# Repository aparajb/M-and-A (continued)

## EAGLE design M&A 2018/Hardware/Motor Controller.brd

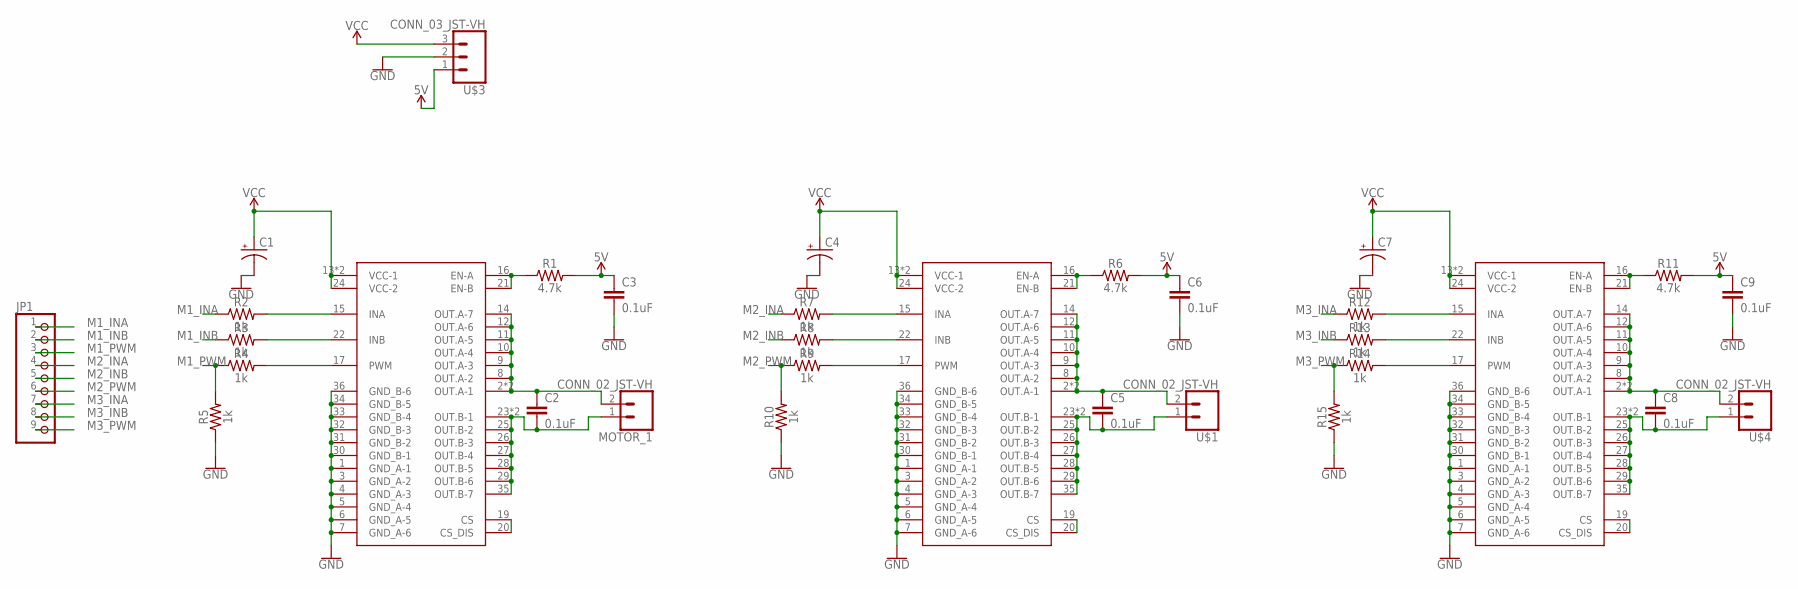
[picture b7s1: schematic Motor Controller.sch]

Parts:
C1, C4, C7: CPOL-USE3.5-8; E3,5-8
C2, C3, C5, C6, C8, C9: 0.1uF; 0603
JP1: PINHD-1X9; 1X09
M1: M1; SOP50P1030X247-36N
M2: M2; SOP50P1030X247-36N
M3: M3; SOP50P1030X247-36N
MOTOR_1: CONN_02_JST-VH; B2P-VH
R1, R6, R11: 4.7k; 0603
R2, R3, R4, R5, R7, R8, R9, R10, R12, R13, R14, R15: 1k; 0603
U$1, U$4: CONN_02_JST-VH; B2P-VH
U$3: CONN_03_JST-VH; B3P-VH

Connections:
5V: C3.1, C6.1, C9.1, R1.2, R6.2, R11.2, U$3.1
GND: C1.-, C3.2, C4.-, C6.2, C7.-, C9.2, M1.1 (GND_A-1), M1.3 (GND_A-2), M1.4 (GND_A-3), M1.5 (GND_A-4), M1.6 (GND_A-5), M1.7 (GND_A-6), M1.30 (GND_B-1), M1.31 (GND_B-2), M1.32 (GND_B-3), M1.33 (GND_B-4), M1.34 (GND_B-5), M1.36 (GND_B-6), M2.1 (GND_A-1), M2.3 (GND_A-2), M2.4 (GND_A-3), M2.5 (GND_A-4), M2.6 (GND_A-5), M2.7 (GND_A-6), M2.30 (GND_B-1), M2.31 (GND_B-2), M2.32 (GND_B-3), M2.33 (GND_B-4), M2.34 (GND_B-5), M2.36 (GND_B-6), M3.1 (GND_A-1), M3.3 (GND_A-2), M3.4 (GND_A-3), M3.5 (GND_A-4), M3.6 (GND_A-5), M3.7 (GND_A-6), M3.30 (GND_B-1), M3.31 (GND_B-2), M3.32 (GND_B-3), M3.33 (GND_B-4), M3.34 (GND_B-5), M3.36 (GND_B-6), R5.1, R10.1, R15.1, U$3.2
M1_INA: JP1.1, R2.1
M1_INB: JP1.2, R3.1
M1_PWM: JP1.3, R4.1, R5.2
M2_INA: JP1.4, R7.1
M2_INB: JP1.5, R8.1
M2_PWM: JP1.6, R9.1, R10.2
M3_INA: JP1.7, R12.1
M3_INB: JP1.8, R13.1
M3_PWM: JP1.9, R14.1, R15.2
unnamed: C5.1, M2.2 (OUT.A-1), M2.8 (OUT.A-2), M2.9 (OUT.A-3), M2.10 (OUT.A-4), M2.11 (OUT.A-5), M2.12 (OUT.A-6), M2.14 (OUT.A-7), M2.SLUG2 (OUT.A-1), U$1.2
unnamed: C2.1, M1.2 (OUT.A-1), M1.8 (OUT.A-2), M1.9 (OUT.A-3), M1.10 (OUT.A-4), M1.11 (OUT.A-5), M1.12 (OUT.A-6), M1.14 (OUT.A-7), M1.SLUG2 (OUT.A-1), MOTOR_1.2
unnamed: C2.2, M1.23 (OUT.B-1), M1.25 (OUT.B-2), M1.26 (OUT.B-3), M1.27 (OUT.B-4), M1.28 (OUT.B-5), M1.29 (OUT.B-6), M1.35 (OUT.B-7), M1.SLUG3 (OUT.B-1), MOTOR_1.1
unnamed: M1.19 (CS), M1.20 (CS_DIS)
unnamed: M1.16 (EN-A), M1.21 (EN-B), R1.1
unnamed: C5.2, M2.23 (OUT.B-1), M2.25 (OUT.B-2), M2.26 (OUT.B-3), M2.27 (OUT.B-4), M2.28 (OUT.B-5), M2.29 (OUT.B-6), M2.35 (OUT.B-7), M2.SLUG3 (OUT.B-1), U$1.1
unnamed: M2.19 (CS), M2.20 (CS_DIS)
unnamed: M1.15 (INA), R2.2
unnamed: M1.22 (INB), R3.2
unnamed: M1.17 (PWM), R4.2
unnamed: M2.16 (EN-A), M2.21 (EN-B), R6.1
unnamed: M2.15 (INA), R7.2
unnamed: M2.22 (INB), R8.2
unnamed: M2.17 (PWM), R9.2
unnamed: C8.1, M3.2 (OUT.A-1), M3.8 (OUT.A-2), M3.9 (OUT.A-3), M3.10 (OUT.A-4), M3.11 (OUT.A-5), M3.12 (OUT.A-6), M3.14 (OUT.A-7), M3.SLUG2 (OUT.A-1), U$4.2
unnamed: C8.2, M3.23 (OUT.B-1), M3.25 (OUT.B-2), M3.26 (OUT.B-3), M3.27 (OUT.B-4), M3.28 (OUT.B-5), M3.29 (OUT.B-6), M3.35 (OUT.B-7), M3.SLUG3 (OUT.B-1), U$4.1
unnamed: M3.19 (CS), M3.20 (CS_DIS)
unnamed: M3.16 (EN-A), M3.21 (EN-B), R11.1
unnamed: M3.15 (INA), R12.2
unnamed: M3.22 (INB), R13.2
unnamed: M3.17 (PWM), R14.2
VCC: C1.+, C4.+, C7.+, M1.13 (VCC-1), M1.24 (VCC-2), M1.SLUG1 (VCC-1), M2.13 (VCC-1), M2.24 (VCC-2), M2.SLUG1 (VCC-1), M3.13 (VCC-1), M3.24 (VCC-2), M3.SLUG1 (VCC-1), U$3.3

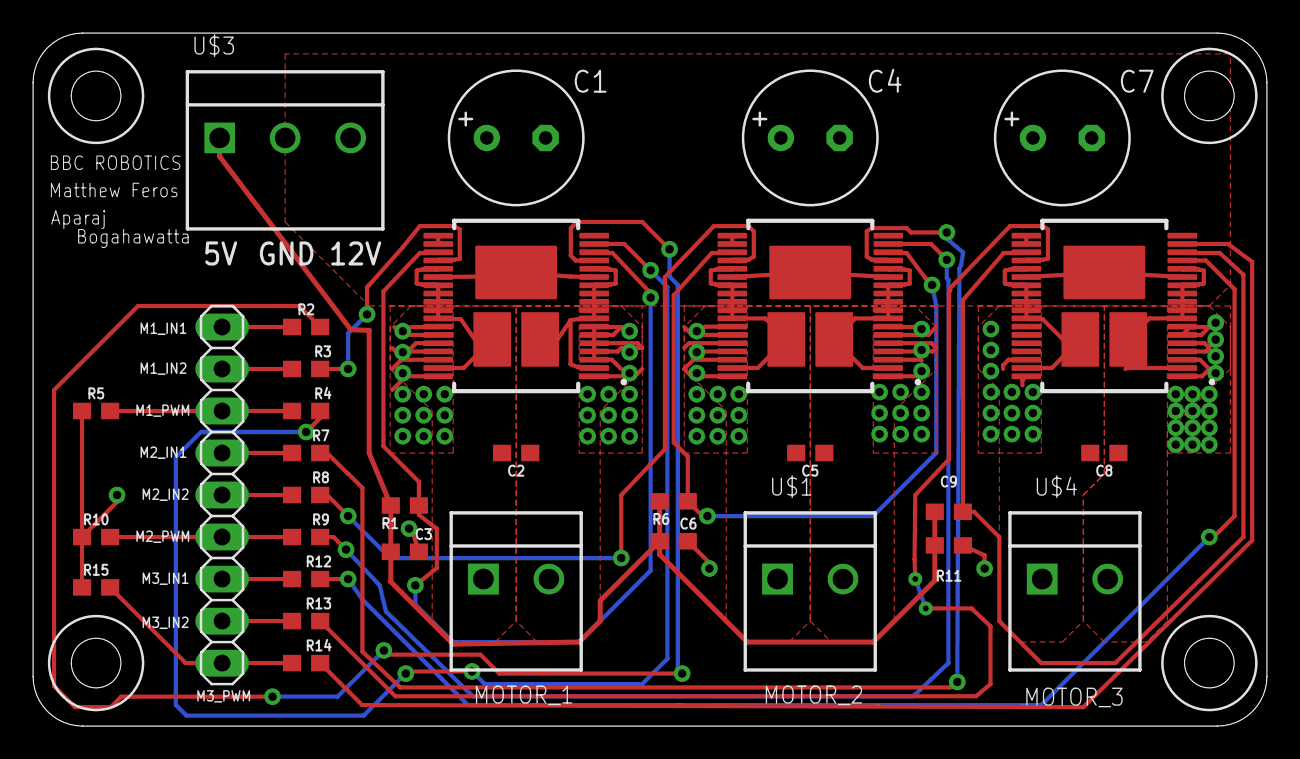
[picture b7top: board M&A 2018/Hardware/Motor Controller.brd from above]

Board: 2 copper layers, 74.6 x 41.9 mm, 32 parts (0 on the bottom side), 33 nets.

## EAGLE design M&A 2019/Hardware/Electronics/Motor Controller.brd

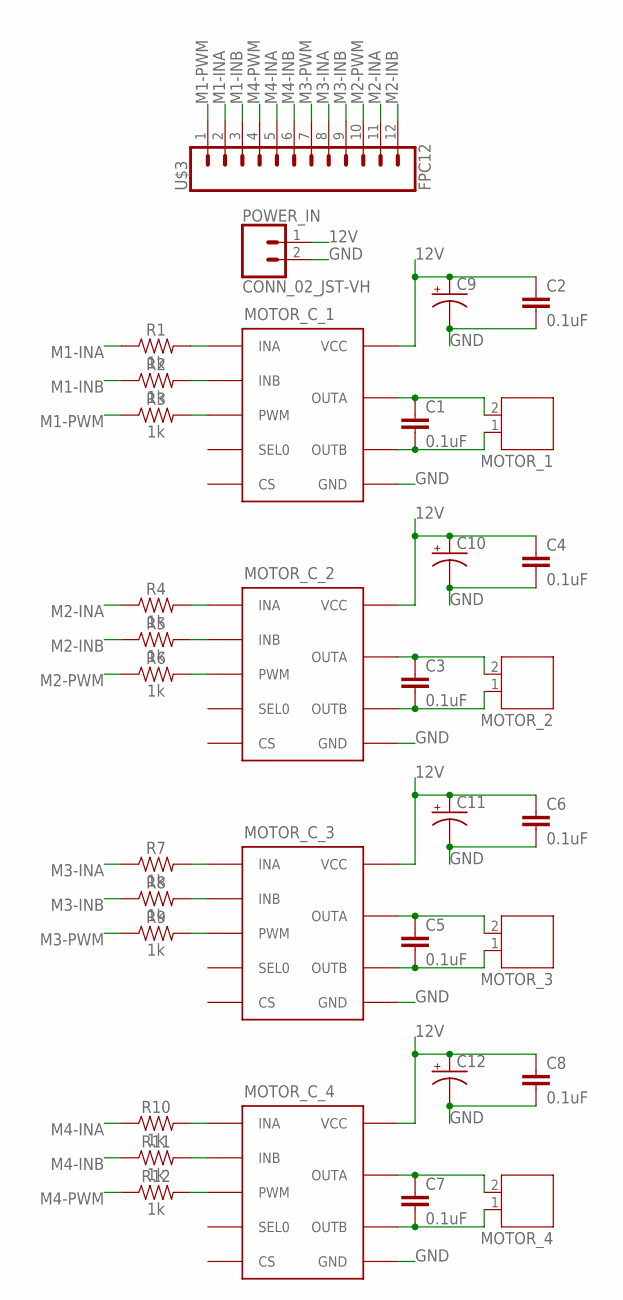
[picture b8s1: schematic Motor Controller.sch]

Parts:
C1, C2, C3, C4, C5, C6, C7, C8: 0.1uF; 0603
C9, C10, C11, C12: CPOL-USE3.5-8; E3,5-8
MOTOR_1, MOTOR_2, MOTOR_3, MOTOR_4: JST-PH2
MOTOR_C_1, MOTOR_C_2, MOTOR_C_3, MOTOR_C_4: VNH7100BASTR; SO-16
POWER_IN: CONN_02_JST-VH; B2P-VH
R1, R2, R3, R4, R5, R6, R7, R8, R9, R10, R11, R12: 1k; 0603
U$3: FPC12

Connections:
12V: C2.1, C4.1, C6.1, C8.1, C9.+, C10.+, C11.+, C12.+, MOTOR_C_1.4 (VCC), MOTOR_C_1.5 (VCC), MOTOR_C_1.12 (VCC), MOTOR_C_2.4 (VCC), MOTOR_C_2.5 (VCC), MOTOR_C_2.12 (VCC), MOTOR_C_3.4 (VCC), MOTOR_C_3.5 (VCC), MOTOR_C_3.12 (VCC), MOTOR_C_4.4 (VCC), MOTOR_C_4.5 (VCC), MOTOR_C_4.12 (VCC), POWER_IN.1
GND: C2.2, C4.2, C6.2, C8.2, C9.-, C10.-, C11.-, C12.-, MOTOR_C_1.1 (GND), MOTOR_C_1.8 (GND), MOTOR_C_1.9 (GND), MOTOR_C_1.16 (GND), MOTOR_C_2.1 (GND), MOTOR_C_2.8 (GND), MOTOR_C_2.9 (GND), MOTOR_C_2.16 (GND), MOTOR_C_3.1 (GND), MOTOR_C_3.8 (GND), MOTOR_C_3.9 (GND), MOTOR_C_3.16 (GND), MOTOR_C_4.1 (GND), MOTOR_C_4.8 (GND), MOTOR_C_4.9 (GND), MOTOR_C_4.16 (GND), POWER_IN.2
M1-INA: R1.1, U$3.2
M1-INB: R2.1, U$3.3
M1-PWM: R3.1, U$3.1
M2-INA: R4.1, U$3.11
M2-INB: R5.1, U$3.12
M2-PWM: R6.1, U$3.10
M3-INA: R7.1, U$3.8
M3-INB: R8.1, U$3.9
M3-PWM: R9.1, U$3.7
M4-INA: R10.1, U$3.5
M4-INB: R11.1, U$3.6
M4-PWM: R12.1, U$3.4
unnamed: MOTOR_C_1.3 (INA), R1.2
unnamed: MOTOR_C_1.6 (INB), R2.2
unnamed: MOTOR_C_2.3 (INA), R4.2
unnamed: MOTOR_C_2.6 (INB), R5.2
unnamed: MOTOR_C_1.11 (PWM), R3.2
unnamed: MOTOR_C_2.11 (PWM), R6.2
unnamed: C3.1, MOTOR_2.2, MOTOR_C_2.2 (OUTA), MOTOR_C_2.15 (OUTA)
unnamed: C1.1, MOTOR_1.2, MOTOR_C_1.2 (OUTA), MOTOR_C_1.15 (OUTA)
unnamed: C1.2, MOTOR_1.1, MOTOR_C_1.7 (OUTB), MOTOR_C_1.10 (OUTB)
unnamed: C3.2, MOTOR_2.1, MOTOR_C_2.7 (OUTB), MOTOR_C_2.10 (OUTB)
unnamed: MOTOR_C_3.3 (INA), R7.2
unnamed: MOTOR_C_3.6 (INB), R8.2
unnamed: MOTOR_C_3.11 (PWM), R9.2
unnamed: C5.1, MOTOR_3.2, MOTOR_C_3.2 (OUTA), MOTOR_C_3.15 (OUTA)
unnamed: C5.2, MOTOR_3.1, MOTOR_C_3.7 (OUTB), MOTOR_C_3.10 (OUTB)
unnamed: MOTOR_C_4.3 (INA), R10.2
unnamed: MOTOR_C_4.6 (INB), R11.2
unnamed: MOTOR_C_4.11 (PWM), R12.2
unnamed: C7.1, MOTOR_4.2, MOTOR_C_4.2 (OUTA), MOTOR_C_4.15 (OUTA)
unnamed: C7.2, MOTOR_4.1, MOTOR_C_4.7 (OUTB), MOTOR_C_4.10 (OUTB)

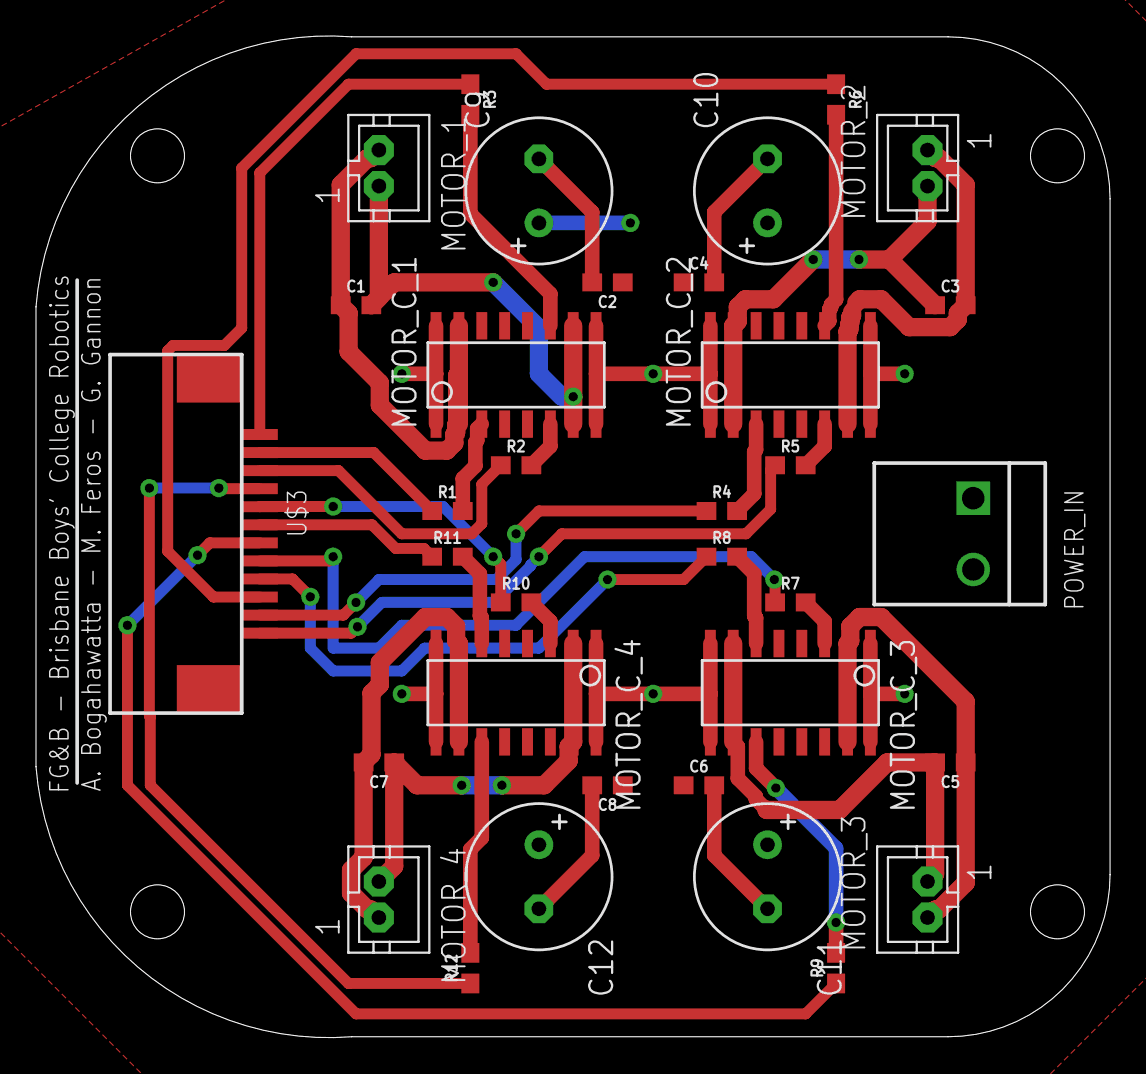
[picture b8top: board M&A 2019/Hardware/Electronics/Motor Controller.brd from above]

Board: 2 copper layers, 59.7 x 55.6 mm, 34 parts (0 on the bottom side), 34 nets.

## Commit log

2019-08-07 added readme
2019-08-08 Fixed readme
2019-08-09 Fixed readme hyperlink
2020-02-27 updating
2020-03-25 code is ready for usage
2021-07-20 Light Sensor Code Done, Re-structured main a bit
2021-07-26 pins
2021-10-07 other stuff
2021-10-08 ur mother is gay
2021-10-09 ur mother is gay too lol
2021-10-10 lolololololol
